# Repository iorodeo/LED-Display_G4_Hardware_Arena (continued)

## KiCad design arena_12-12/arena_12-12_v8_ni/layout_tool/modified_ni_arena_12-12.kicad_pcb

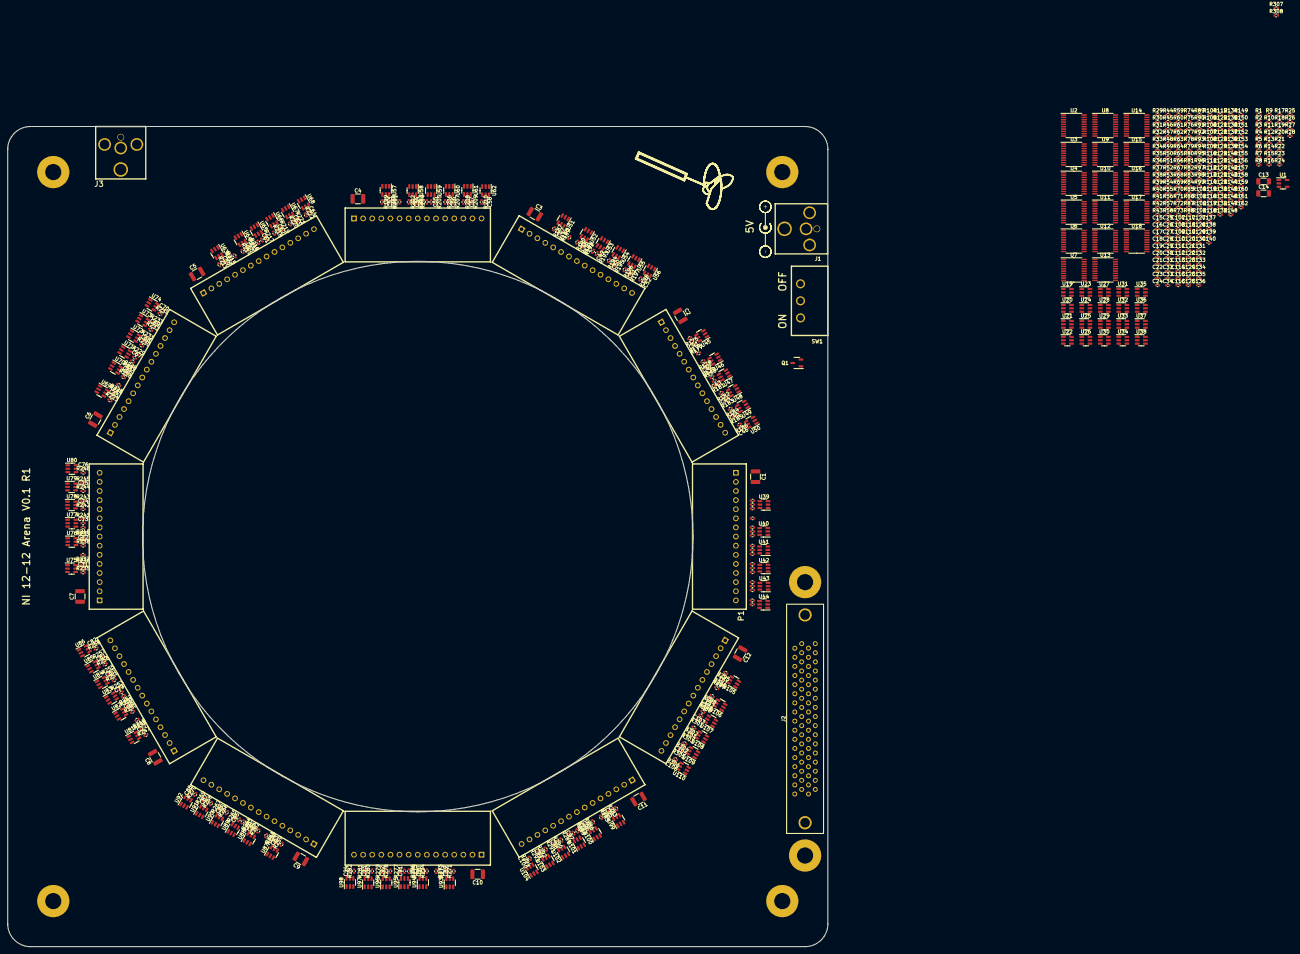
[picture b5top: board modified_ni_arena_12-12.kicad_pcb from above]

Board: 4 copper layers, 228.6 x 228.6 mm, 581 parts (0 on the bottom side), 658 nets, no tracks yet.

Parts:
C1, C2, C3, C4, C5, C6, C7, C8, C9, C10, C11, C12: 100uF; C_1210_3225Metric
C13, C14: 10uF; C_1206_3216Metric
C15, C16, C17, C18, C19, C20, C21, C22, C23, C24, C25, C26, C27, C28, C29, C30, C31, C32, C33, C34, C35, C36, C37, C38, C39, C40, C41, C42, C43, C44, C45, C46, C47, C48, C49, C50, C51, C52, C53, C54, C55, C56, C57, C58, C59, C60, C61, C62, C63, C64, C65, C66, C67, C68, C69, C70, C71, C72, C73, C74, C75, C76, C77, C78, C79, C80, C81, C82, C83, C84, C85, C86, C87, C88, C89, C90, C91, C92, C93, C94, C95, C96, C97, C98, C99, C100, C101, C102, C103, C104, C105, C106, C107, C108, C109, C110, C111, C112, C113, C114, C115, C116, C117, C118, C119, C120, C121, C122, C123, C124, C125, C126, C127, C128, C129, C130, C131, C132, C133, C134, C135, C136, C137, C138, C139, C140: 0.1uF; C_0402_1005Metric
H1, H2, H3, H4, H5, H6: MountingHole_Pad; MountingHole_4.5mm_Pad
J1, J3: Barrel_Jack; DCJACK_2PIN_HIGHCURRENT
J2: NI_TE_68pos; TE_CONN_DSUB_VERT_68
P1, P2, P3, P4, P5, P6, P7, P8, P9, P10, P11, P12: CONN15; HEADER_TOP
Q1: MOSFET_NCHAN; SOT-23-3
R1, R2, R3, R4, R5, R6, R7, R8, R9, R10, R11, R12, R13, R14, R15, R16, R17, R18, R19, R20, R21, R22, R23, R24, R25, R26, R27, R28, R29, R30, R31, R32, R33, R34, R35, R36, R37, R38, R39, R40, R41, R42, R43, R44, R45, R46, R47, R48, R49, R50, R51, R52, R53, R54, R55, R56, R57, R58, R59, R60, R61, R62, R63, R64, R65, R66, R67, R68, R69, R70, R71, R72, R73, R74, R75, R76, R77, R78, R79, R80, R81, R82, R83, R84, R85, R86, R87, R88, R89, R90, R91, R92, R93, R94, R95, R96, R97, R98, R99, R100, R101, R102, R103, R104, R105, R106, R107, R108, R109, R110, R111, R112, R113, R114, R115, R116, R117, R118, R119, R120, R121, R122, R123, R124, R125, R126, R127, R128, R129, R130, R131, R132, R133, R134, R135, R136, R137, R138, R139, R140, R141, R142, R143, R144, R145, R146, R147, R148, R149, R150, R151, R152, R153, R154, R155, R156, R157, R158, R159, R160, R161, R162, R163, R164, R165, R166, R167, R168, R169, R170, R171, R172, R173, R174, R175, R176, R177, R178, R179, R180, R181, R182, R183, R184, R185, R186, R187, R188, R189, R190, R191, R192, R193, R194, R195, R196, R197, R198, R199, R200, R201, R202, R203, R204, R205, R206, R207, R208, R209, R210, R211, R212, R213, R214, R215, R216, R217, R218, R219, R220, R221, R222, R223, R224, R225, R226, R227, R228, R229, R230, R231, R232, R233, R234, R235, R236, R237, R238, R239, R240, R241, R242, R243, R244, R245, R246, R247, R248, R249, R250, R251, R252, R253, R254, R255, R256, R257, R258, R259, R260, R261, R262, R263, R264, R265, R266, R267, R268, R269, R270, R271, R272, R273, R274, R275, R276, R277, R278, R279, R280, R281, R282, R283, R284, R285, R286, R287, R288, R289, R290, R291, R292, R293, R294, R295, R296, R297, R298, R299, R300, R301, R302, R303, R304, R305, R306: 33; R_0402_1005Metric
R307: 20k; R_0402_1005Metric
R308: 200; R_0402_1005Metric
SW1: SW_SPDT; slide_switch
U1: AP2112K-3.3; SOT-23-5
U2, U3, U4, U5, U6, U7, U8, U9, U10, U11, U12, U13, U14, U15, U16, U17, U18: TXB0108PW; TSSOP-20_4.4x6.5mm_P0.65mm
U19, U20, U21, U22, U23, U24, U25, U26, U27, U28, U29, U30, U31, U32, U33, U34, U35, U36, U37, U38, U39, U40, U41, U42, U43, U44, U45, U46, U47, U48, U49, U50, U51, U52, U53, U54, U55, U56, U57, U58, U59, U60, U61, U62, U63, U64, U65, U66, U67, U68, U69, U70, U71, U72, U73, U74, U75, U76, U77, U78, U79, U80, U81, U82, U83, U84, U85, U86, U87, U88, U89, U90, U91, U92, U93, U94, U95, U96, U97, U98, U99, U100, U101, U102, U103, U104, U105, U106, U107, U108, U109, U110: 74LVC2G17; SOT-23-6

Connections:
+3.3V: C14.1, C15.1, C16.1, C17.1, C18.1, C19.1, C20.1, C21.1, C22.1, C23.1, C24.1, C25.1, C26.1, C27.1, C28.1, C29.1, C30.1, C31.1, C32.1, C33.1, C34.1, C107.1, C109.1, C111.1, C113.1, C115.1, C117.1, C119.1, C121.1, C123.1, C125.1, C127.1, C129.1, C131.1, C133.1, C135.1, C137.1, C139.1, U1.5 (VOUT), U2.2 (VCCA), U2.10 (OE), U3.2 (VCCA), U3.10 (OE), U4.2 (VCCA), U4.10 (OE), U5.2 (VCCA), U5.10 (OE), U6.2 (VCCA), U6.10 (OE), U7.2 (VCCA), U7.10 (OE), U8.2 (VCCA), U8.10 (OE), U9.2 (VCCA), U9.10 (OE), U10.2 (VCCA), U10.10 (OE), U11.2 (VCCA), U11.10 (OE), U12.2 (VCCA), U12.10 (OE), U13.2 (VCCA), U13.10 (OE), U14.2 (VCCA), U14.10 (OE), U15.2 (VCCA), U15.10 (OE), U16.2 (VCCA), U16.10 (OE), U17.2 (VCCA), U17.10 (OE), U18.2 (VCCA), U18.10 (OE), U19.5 (VCC), U20.5 (VCC), U21.5 (VCC), U22.5 (VCC), U23.5 (VCC), U24.5 (VCC), U25.5 (VCC), U26.5 (VCC), U27.5 (VCC), U28.5 (VCC), U29.5 (VCC), U30.5 (VCC), U31.5 (VCC), U32.5 (VCC), U33.5 (VCC), U34.5 (VCC), U35.5 (VCC), U36.5 (VCC), U37.5 (VCC), U38.5 (VCC)
+5V: C1.1, C2.1, C3.1, C4.1, C5.1, C6.1, C7.1, C8.1, C9.1, C10.1, C11.1, C12.1, C13.1, C35.1, C36.1, C37.1, C38.1, C39.1, C40.1, C41.1, C42.1, C43.1, C44.1, C45.1, C46.1, C47.1, C48.1, C49.1, C50.1, C51.1, C52.1, C53.1, C54.1, C55.1, C56.1, C57.1, C58.1, C59.1, C60.1, C61.1, C62.1, C63.1, C64.1, C65.1, C66.1, C67.1, C68.1, C69.1, C70.1, C71.1, C72.1, C73.1, C74.1, C75.1, C76.1, C77.1, C78.1, C79.1, C80.1, C81.1, C82.1, C83.1, C84.1, C85.1, C86.1, C87.1, C88.1, C89.1, C90.1, C91.1, C92.1, C93.1, C94.1, C95.1, C96.1, C97.1, C98.1, C99.1, C100.1, C101.1, C102.1, C103.1, C104.1, C105.1, C106.1, C108.1, C110.1, C112.1, C114.1, C116.1, C118.1, C120.1, C122.1, C124.1, C126.1, C128.1, C130.1, C132.1, C134.1, C136.1, C138.1, C140.1, J3.1, P1.1, P2.1, P3.1, P4.1, P5.1, P6.1, P7.1, P8.1, P9.1, P10.1, P11.1, P12.1, SW1.2 (B), U1.1 (VIN), U1.3 (EN), U2.19 (VCCB), U3.19 (VCCB), U4.19 (VCCB), U5.19 (VCCB), U6.19 (VCCB), U7.19 (VCCB), U8.19 (VCCB), U9.19 (VCCB), U10.19 (VCCB), U11.19 (VCCB), U12.19 (VCCB), U13.19 (VCCB), U14.19 (VCCB), U15.19 (VCCB), U16.19 (VCCB), U17.19 (VCCB), U18.19 (VCCB), U39.5 (VCC), U40.5 (VCC), U41.5 (VCC), U42.5 (VCC), U43.5 (VCC), U44.5 (VCC), U45.5 (VCC), U46.5 (VCC), U47.5 (VCC), U48.5 (VCC), U49.5 (VCC), U50.5 (VCC), U51.5 (VCC), U52.5 (VCC), U53.5 (VCC), U54.5 (VCC), U55.5 (VCC), U56.5 (VCC), U57.5 (VCC), U58.5 (VCC), U59.5 (VCC), U60.5 (VCC), U61.5 (VCC), U62.5 (VCC), U63.5 (VCC), U64.5 (VCC), U65.5 (VCC), U66.5 (VCC), U67.5 (VCC), U68.5 (VCC), U69.5 (VCC), U70.5 (VCC), U71.5 (VCC), U72.5 (VCC), U73.5 (VCC), U74.5 (VCC), U75.5 (VCC), U76.5 (VCC), U77.5 (VCC), U78.5 (VCC), U79.5 (VCC), U80.5 (VCC), U81.5 (VCC), U82.5 (VCC), U83.5 (VCC), U84.5 (VCC), U85.5 (VCC), U86.5 (VCC), U87.5 (VCC), U88.5 (VCC), U89.5 (VCC), U90.5 (VCC), U91.5 (VCC), U92.5 (VCC), U93.5 (VCC), U94.5 (VCC), U95.5 (VCC), U96.5 (VCC), U97.5 (VCC), U98.5 (VCC), U99.5 (VCC), U100.5 (VCC), U101.5 (VCC), U102.5 (VCC), U103.5 (VCC), U104.5 (VCC), U105.5 (VCC), U106.5 (VCC), U107.5 (VCC), U108.5 (VCC), U109.5 (VCC), U110.5 (VCC)
/Level Shifters/PAN3V.CS_0: R1.2, U19.1
/Level Shifters/PAN3V.CS_1: R2.2, U19.3
/Level Shifters/PAN3V.CS_2: R3.2, U20.1
/Level Shifters/PAN3V.CS_3: R4.2, U20.3
/Level Shifters/PAN3V.CS_4: R5.2, U21.1
/Level Shifters/PAN3V.CS_5: R6.2, U21.3
/Level Shifters/PAN3V.CS_6: R7.2, U22.1
/Level Shifters/PAN3V.CS_7: R8.2, U22.3
/Level Shifters/PAN3V.EXT_INT: R22.2, U38.1
/Level Shifters/PAN3V.MISO_00: J2.50, R149.2
/Level Shifters/PAN3V.MISO_01: J2.52, R150.2
/Level Shifters/PAN3V.MISO_02: J2.54, R151.2
/Level Shifters/PAN3V.MISO_03: J2.56, R152.2
/Level Shifters/PAN3V.MISO_04: J2.58, R153.2
/Level Shifters/PAN3V.MISO_05: J2.60, R154.2
/Level Shifters/PAN3V.MISO_06: J2.62, R155.2
/Level Shifters/PAN3V.MISO_07: J2.63, R156.2
/Level Shifters/PAN3V.MISO_08: J2.64, R159.1
/Level Shifters/PAN3V.MISO_09: J2.65, R160.1
/Level Shifters/PAN3V.MISO_10: J2.66, R161.1
/Level Shifters/PAN3V.MISO_11: J2.67, R162.1
/Level Shifters/PAN3V.MOSI_00: R15.2, U26.1
/Level Shifters/PAN3V.MOSI_01: R16.2, U26.3
/Level Shifters/PAN3V.MOSI_02: R17.2, U27.1
/Level Shifters/PAN3V.MOSI_03: R18.2, U27.3
/Level Shifters/PAN3V.MOSI_04: R19.2, U32.1
/Level Shifters/PAN3V.MOSI_05: R20.2, U32.3
/Level Shifters/PAN3V.MOSI_06: R21.2, U34.1
/Level Shifters/PAN3V.MOSI_07: R23.2, U34.3
/Level Shifters/PAN3V.MOSI_08: R24.2, U33.1
/Level Shifters/PAN3V.MOSI_09: R25.2, U33.3
/Level Shifters/PAN3V.MOSI_10: R26.2, U35.1
/Level Shifters/PAN3V.MOSI_11: R27.2, U35.3
/Level Shifters/PAN3V.RESET: R28.2, U38.3
/Level Shifters/PAN3V.SCK_0: R9.2, U23.1
/Level Shifters/PAN3V.SCK_1: R10.2, U23.3
/Level Shifters/PAN3V.SCK_2: R11.2, U24.1
/Level Shifters/PAN3V.SCK_3: R12.2, U24.3
/Level Shifters/PAN3V.SCK_4: R13.2, U25.1
/Level Shifters/PAN3V.SCK_5: R14.2, U25.3
/Level Shifters/PAN5V.CS_0_P01: R29.1, U40.3
/Level Shifters/PAN5V.CS_0_P02: R30.1, U46.1
/Level Shifters/PAN5V.CS_0_P03: R31.1, U52.1
/Level Shifters/PAN5V.CS_0_P04: R32.1, U58.1
/Level Shifters/PAN5V.CS_0_P05: R33.1, U64.1
/Level Shifters/PAN5V.CS_0_P06: R34.1, U70.1
/Level Shifters/PAN5V.CS_0_P07: R35.1, U76.1
/Level Shifters/PAN5V.CS_0_P08: R36.1, U82.1
/Level Shifters/PAN5V.CS_0_P09: R37.1, U88.1
/Level Shifters/PAN5V.CS_0_P10: R38.1, U94.1
/Level Shifters/PAN5V.CS_0_P11: R39.1, U100.1
/Level Shifters/PAN5V.CS_0_P12: R40.1, U106.1
/Level Shifters/PAN5V.CS_1_P01: R41.1, U40.1
/Level Shifters/PAN5V.CS_1_P02: R42.1, U46.3
/Level Shifters/PAN5V.CS_1_P03: R43.1, U52.3
/Level Shifters/PAN5V.CS_1_P04: R44.1, U58.3
/Level Shifters/PAN5V.CS_1_P05: R45.1, U64.3
/Level Shifters/PAN5V.CS_1_P06: R46.1, U70.3
/Level Shifters/PAN5V.CS_1_P07: R47.1, U76.3
/Level Shifters/PAN5V.CS_1_P08: R48.1, U82.3
/Level Shifters/PAN5V.CS_1_P09: R49.1, U88.3
/Level Shifters/PAN5V.CS_1_P10: R50.1, U94.3
/Level Shifters/PAN5V.CS_1_P11: R51.1, U100.3
/Level Shifters/PAN5V.CS_1_P12: R52.1, U106.3
/Level Shifters/PAN5V.CS_2_P01: R53.1, U41.3
/Level Shifters/PAN5V.CS_2_P02: R54.1, U47.1
/Level Shifters/PAN5V.CS_2_P03: R55.1, U53.1
/Level Shifters/PAN5V.CS_2_P04: R56.1, U59.1
/Level Shifters/PAN5V.CS_2_P05: R57.1, U65.1
/Level Shifters/PAN5V.CS_2_P06: R58.1, U71.1
/Level Shifters/PAN5V.CS_2_P07: R59.1, U77.1
/Level Shifters/PAN5V.CS_2_P08: R60.1, U83.1
/Level Shifters/PAN5V.CS_2_P09: R61.1, U89.1
/Level Shifters/PAN5V.CS_2_P10: R62.1, U95.1
/Level Shifters/PAN5V.CS_2_P11: R63.1, U101.1
/Level Shifters/PAN5V.CS_2_P12: R64.1, U107.1
/Level Shifters/PAN5V.CS_3_P01: R65.1, U41.1
/Level Shifters/PAN5V.CS_3_P02: R66.1, U47.3
/Level Shifters/PAN5V.CS_3_P03: R67.1, U53.3
/Level Shifters/PAN5V.CS_3_P04: R68.1, U59.3
/Level Shifters/PAN5V.CS_3_P05: R69.1, U65.3
/Level Shifters/PAN5V.CS_3_P06: R70.1, U71.3
/Level Shifters/PAN5V.CS_3_P07: R71.1, U77.3
/Level Shifters/PAN5V.CS_3_P08: R72.1, U83.3
/Level Shifters/PAN5V.CS_3_P09: R73.1, U89.3
/Level Shifters/PAN5V.CS_3_P10: R74.1, U95.3
/Level Shifters/PAN5V.CS_3_P11: R75.1, U101.3
/Level Shifters/PAN5V.CS_3_P12: R76.1, U107.3
/Level Shifters/PAN5V.CS_4_P01: R77.1, U42.3
/Level Shifters/PAN5V.CS_4_P02: R78.1, U48.1
/Level Shifters/PAN5V.CS_4_P03: R79.1, U54.1
/Level Shifters/PAN5V.CS_4_P04: R80.1, U60.1
/Level Shifters/PAN5V.CS_4_P05: R81.1, U66.1
/Level Shifters/PAN5V.CS_4_P06: R82.1, U72.1
/Level Shifters/PAN5V.CS_4_P07: R83.1, U78.1
/Level Shifters/PAN5V.CS_4_P08: R84.1, U84.1
/Level Shifters/PAN5V.CS_4_P09: R85.1, U90.1
/Level Shifters/PAN5V.CS_4_P10: R86.1, U96.1
/Level Shifters/PAN5V.CS_4_P11: R87.1, U102.1
/Level Shifters/PAN5V.CS_4_P12: R88.1, U108.1
/Level Shifters/PAN5V.CS_5_P01: R89.1, U42.1
/Level Shifters/PAN5V.CS_5_P02: R90.1, U48.3
/Level Shifters/PAN5V.CS_5_P03: R91.1, U54.3
/Level Shifters/PAN5V.CS_5_P04: R92.1, U60.3
/Level Shifters/PAN5V.CS_5_P05: R93.1, U66.3
/Level Shifters/PAN5V.CS_5_P06: R94.1, U72.3
/Level Shifters/PAN5V.CS_5_P07: R95.1, U78.3
/Level Shifters/PAN5V.CS_5_P08: R96.1, U84.3
/Level Shifters/PAN5V.CS_5_P09: R97.1, U90.3
/Level Shifters/PAN5V.CS_5_P10: R98.1, U96.3
/Level Shifters/PAN5V.CS_5_P11: R99.1, U102.3
/Level Shifters/PAN5V.CS_5_P12: R100.1, U108.3
/Level Shifters/PAN5V.CS_6_P01: R101.1, U43.3
/Level Shifters/PAN5V.CS_6_P02: R102.1, U49.1
/Level Shifters/PAN5V.CS_6_P03: R103.1, U55.1
/Level Shifters/PAN5V.CS_6_P04: R104.1, U61.1
/Level Shifters/PAN5V.CS_6_P05: R105.1, U67.1
/Level Shifters/PAN5V.CS_6_P06: R106.1, U73.1
/Level Shifters/PAN5V.CS_6_P07: R107.1, U79.1
/Level Shifters/PAN5V.CS_6_P08: R108.1, U85.1
/Level Shifters/PAN5V.CS_6_P09: R109.1, U91.1
/Level Shifters/PAN5V.CS_6_P10: R110.1, U97.1
/Level Shifters/PAN5V.CS_6_P11: R111.1, U103.1
/Level Shifters/PAN5V.CS_6_P12: R112.1, U109.1
/Level Shifters/PAN5V.CS_7_P01: R113.1, U43.1
/Level Shifters/PAN5V.CS_7_P02: R114.1, U49.3
/Level Shifters/PAN5V.CS_7_P03: R115.1, U55.3
/Level Shifters/PAN5V.CS_7_P04: R116.1, U61.3
/Level Shifters/PAN5V.CS_7_P05: R117.1, U67.3
/Level Shifters/PAN5V.CS_7_P06: R118.1, U73.3
/Level Shifters/PAN5V.CS_7_P07: R119.1, U79.3
/Level Shifters/PAN5V.CS_7_P08: R120.1, U85.3
/Level Shifters/PAN5V.CS_7_P09: R121.1, U91.3
/Level Shifters/PAN5V.CS_7_P10: R122.1, U97.3
/Level Shifters/PAN5V.CS_7_P11: R123.1, U103.3
/Level Shifters/PAN5V.CS_7_P12: R124.1, U109.3
/Level Shifters/PAN5V.EXT_INT: R157.1, U44.3, U50.1, U56.1, U62.1, U68.1, U74.1, U80.1, U86.1, U92.1, U98.1, U104.1, U110.1
/Level Shifters/PAN5V.MISO_00: R165.1, U28.1
/Level Shifters/PAN5V.MISO_01: R177.1, U28.3
/Level Shifters/PAN5V.MISO_02: R189.1, U29.1
/Level Shifters/PAN5V.MISO_03: R201.1, U29.3
/Level Shifters/PAN5V.MISO_04: R213.1, U30.1
/Level Shifters/PAN5V.MISO_05: R225.1, U30.3
/Level Shifters/PAN5V.MISO_06: R237.1, U31.1
/Level Shifters/PAN5V.MISO_07: R249.1, U31.3
/Level Shifters/PAN5V.MISO_08: R261.1, U36.1
/Level Shifters/PAN5V.MISO_09: R273.1, U36.3
/Level Shifters/PAN5V.MISO_10: R285.1, U37.1
/Level Shifters/PAN5V.MISO_11: R297.1, U37.3
/Level Shifters/PAN5V.MOSI_00: R137.1, U39.1
/Level Shifters/PAN5V.MOSI_01: R138.1, U45.3
/Level Shifters/PAN5V.MOSI_02: R139.1, U51.3
/Level Shifters/PAN5V.MOSI_03: R140.1, U57.3
/Level Shifters/PAN5V.MOSI_04: R141.1, U63.3
/Level Shifters/PAN5V.MOSI_05: R142.1, U69.3
/Level Shifters/PAN5V.MOSI_06: R143.1, U75.3
/Level Shifters/PAN5V.MOSI_07: R144.1, U81.3
/Level Shifters/PAN5V.MOSI_08: R145.1, U87.3
/Level Shifters/PAN5V.MOSI_09: R146.1, U93.3
/Level Shifters/PAN5V.MOSI_10: R147.1, U99.3
/Level Shifters/PAN5V.MOSI_11: R148.1, U105.3
/Level Shifters/PAN5V.RESET: R158.1, R308.2
/Level Shifters/PAN5V.SCK_0_H1: R125.1, U39.3
/Level Shifters/PAN5V.SCK_0_H2: R126.1, U75.1
/Level Shifters/PAN5V.SCK_1_H1: R127.1, U45.1
/Level Shifters/PAN5V.SCK_1_H2: R128.1, U81.1
/Level Shifters/PAN5V.SCK_2_H1: R129.1, U51.1
/Level Shifters/PAN5V.SCK_2_H2: R130.1, U87.1
/Level Shifters/PAN5V.SCK_3_H1: R131.1, U57.1
/Level Shifters/PAN5V.SCK_3_H2: R132.1, U93.1
/Level Shifters/PAN5V.SCK_4_H1: R133.1, U63.1
/Level Shifters/PAN5V.SCK_4_H2: R134.1, U99.1
/Level Shifters/PAN5V.SCK_5_H1: R135.1, U69.1
/Level Shifters/PAN5V.SCK_5_H2: R136.1, U105.1
/Panel Headers/CS_00_P01: P1.7, R166.2
/Panel Headers/CS_00_P02: P2.7, R178.2
/Panel Headers/CS_00_P03: P3.7, R190.2
/Panel Headers/CS_00_P04: P4.7, R202.2
/Panel Headers/CS_00_P05: P5.7, R214.2
/Panel Headers/CS_00_P06: P6.7, R226.2
/Panel Headers/CS_00_P07: P7.7, R238.2
/Panel Headers/CS_00_P08: P8.7, R250.2
/Panel Headers/CS_00_P09: P9.7, R262.2
/Panel Headers/CS_00_P10: P10.7, R274.2
/Panel Headers/CS_00_P11: P11.7, R286.2
/Panel Headers/CS_00_P12: P12.7, R298.2
/Panel Headers/CS_01_P01: P1.8, R167.2
/Panel Headers/CS_01_P02: P2.8, R179.2
/Panel Headers/CS_01_P03: P3.8, R191.2
/Panel Headers/CS_01_P04: P4.8, R203.2
/Panel Headers/CS_01_P05: P5.8, R215.2
/Panel Headers/CS_01_P06: P6.8, R227.2
/Panel Headers/CS_01_P07: P7.8, R239.2
/Panel Headers/CS_01_P08: P8.8, R251.2
/Panel Headers/CS_01_P09: P9.8, R263.2
/Panel Headers/CS_01_P10: P10.8, R275.2
/Panel Headers/CS_01_P11: P11.8, R287.2
/Panel Headers/CS_01_P12: P12.8, R299.2
/Panel Headers/CS_02_P01: P1.9, R168.2
/Panel Headers/CS_02_P02: P2.9, R180.2
/Panel Headers/CS_02_P03: P3.9, R192.2
/Panel Headers/CS_02_P04: P4.9, R204.2
/Panel Headers/CS_02_P05: P5.9, R216.2
/Panel Headers/CS_02_P06: P6.9, R228.2
/Panel Headers/CS_02_P07: P7.9, R240.2
/Panel Headers/CS_02_P08: P8.9, R252.2
/Panel Headers/CS_02_P09: P9.9, R264.2
/Panel Headers/CS_02_P10: P10.9, R276.2
/Panel Headers/CS_02_P11: P11.9, R288.2
/Panel Headers/CS_02_P12: P12.9, R300.2
/Panel Headers/CS_03_P01: P1.10, R169.2
/Panel Headers/CS_03_P02: P2.10, R181.2
/Panel Headers/CS_03_P03: P3.10, R193.2
/Panel Headers/CS_03_P04: P4.10, R205.2
/Panel Headers/CS_03_P05: P5.10, R217.2
/Panel Headers/CS_03_P06: P6.10, R229.2
/Panel Headers/CS_03_P07: P7.10, R241.2
/Panel Headers/CS_03_P08: P8.10, R253.2
/Panel Headers/CS_03_P09: P9.10, R265.2
/Panel Headers/CS_03_P10: P10.10, R277.2
/Panel Headers/CS_03_P11: P11.10, R289.2
/Panel Headers/CS_03_P12: P12.10, R301.2
/Panel Headers/CS_04_P01: P1.11, R170.2
/Panel Headers/CS_04_P02: P2.11, R182.2
/Panel Headers/CS_04_P03: P3.11, R194.2
/Panel Headers/CS_04_P04: P4.11, R206.2
/Panel Headers/CS_04_P05: P5.11, R218.2
/Panel Headers/CS_04_P06: P6.11, R230.2
/Panel Headers/CS_04_P07: P7.11, R242.2
/Panel Headers/CS_04_P08: P8.11, R254.2
/Panel Headers/CS_04_P09: P9.11, R266.2
/Panel Headers/CS_04_P10: P10.11, R278.2
/Panel Headers/CS_04_P11: P11.11, R290.2
/Panel Headers/CS_04_P12: P12.11, R302.2
/Panel Headers/CS_05_P01: P1.12, R171.2
/Panel Headers/CS_05_P02: P2.12, R183.2
/Panel Headers/CS_05_P03: P3.12, R195.2
/Panel Headers/CS_05_P04: P4.12, R207.2
/Panel Headers/CS_05_P05: P5.12, R219.2
/Panel Headers/CS_05_P06: P6.12, R231.2
/Panel Headers/CS_05_P07: P7.12, R243.2
/Panel Headers/CS_05_P08: P8.12, R255.2
/Panel Headers/CS_05_P09: P9.12, R267.2
/Panel Headers/CS_05_P10: P10.12, R279.2
/Panel Headers/CS_05_P11: P11.12, R291.2
/Panel Headers/CS_05_P12: P12.12, R303.2
/Panel Headers/CS_06_P01: P1.13, R172.2
/Panel Headers/CS_06_P02: P2.13, R184.2
/Panel Headers/CS_06_P03: P3.13, R196.2
/Panel Headers/CS_06_P04: P4.13, R208.2
/Panel Headers/CS_06_P05: P5.13, R220.2
/Panel Headers/CS_06_P06: P6.13, R232.2
/Panel Headers/CS_06_P07: P7.13, R244.2
/Panel Headers/CS_06_P08: P8.13, R256.2
/Panel Headers/CS_06_P09: P9.13, R268.2
/Panel Headers/CS_06_P10: P10.13, R280.2
/Panel Headers/CS_06_P11: P11.13, R292.2
/Panel Headers/CS_06_P12: P12.13, R304.2
/Panel Headers/CS_07_P01: P1.14, R173.2
/Panel Headers/CS_07_P02: P2.14, R185.2
/Panel Headers/CS_07_P03: P3.14, R197.2
/Panel Headers/CS_07_P04: P4.14, R209.2
/Panel Headers/CS_07_P05: P5.14, R221.2
/Panel Headers/CS_07_P06: P6.14, R233.2
/Panel Headers/CS_07_P07: P7.14, R245.2
/Panel Headers/CS_07_P08: P8.14, R257.2
/Panel Headers/CS_07_P09: P9.14, R269.2
/Panel Headers/CS_07_P10: P10.14, R281.2
/Panel Headers/CS_07_P11: P11.14, R293.2
/Panel Headers/CS_07_P12: P12.14, R305.2
/Panel Headers/EXT_INT_P01: P1.15, R174.2
/Panel Headers/EXT_INT_P02: P2.15, R186.2
/Panel Headers/EXT_INT_P03: P3.15, R198.2
/Panel Headers/EXT_INT_P04: P4.15, R210.2
/Panel Headers/EXT_INT_P05: P5.15, R222.2
/Panel Headers/EXT_INT_P06: P6.15, R234.2
/Panel Headers/EXT_INT_P07: P7.15, R246.2
/Panel Headers/EXT_INT_P08: P8.15, R258.2
/Panel Headers/EXT_INT_P09: P9.15, R270.2
/Panel Headers/EXT_INT_P10: P10.15, R282.2
/Panel Headers/EXT_INT_P11: P11.15, R294.2
/Panel Headers/EXT_INT_P12: P12.15, R306.2
/Panel Headers/MISO_00_P01: P1.6, R165.2
/Panel Headers/MISO_01_P02: P2.6, R177.2
/Panel Headers/MISO_02_P03: P3.6, R189.2
/Panel Headers/MISO_03_P04: P4.6, R201.2
/Panel Headers/MISO_04_P05: P5.6, R213.2
/Panel Headers/MISO_05_P06: P6.6, R225.2
/Panel Headers/MISO_06_P07: P7.6, R237.2
/Panel Headers/MISO_07_P08: P8.6, R249.2
/Panel Headers/MISO_08_P09: P9.6, R261.2
/Panel Headers/MISO_09_P10: P10.6, R273.2
/Panel Headers/MISO_10_P11: P11.6, R285.2
/Panel Headers/MISO_11_P12: P12.6, R297.2
/Panel Headers/MOSI_00_P01: P1.5, R164.2
/Panel Headers/MOSI_01_P02: P2.5, R176.2
/Panel Headers/MOSI_02_P03: P3.5, R188.2
/Panel Headers/MOSI_03_P04: P4.5, R200.2
/Panel Headers/MOSI_04_P05: P5.5, R212.2
/Panel Headers/MOSI_05_P06: P6.5, R224.2
/Panel Headers/MOSI_06_P07: P7.5, R236.2
/Panel Headers/MOSI_07_P08: P8.5, R248.2
/Panel Headers/MOSI_08_P09: P9.5, R260.2
/Panel Headers/MOSI_09_P10: P10.5, R272.2
/Panel Headers/MOSI_10_P11: P11.5, R284.2
/Panel Headers/MOSI_11_P12: P12.5, R296.2
/Panel Headers/RESET: P1.3, P2.3, P3.3, P4.3, P5.3, P6.3, P7.3, P8.3, P9.3, P10.3, P11.3, P12.3, Q1.3 (D)
/Panel Headers/SCK_0_H1_P01: P1.4, R163.2
/Panel Headers/SCK_0_H2_P07: P7.4, R235.2
/Panel Headers/SCK_1_H1_P02: P2.4, R175.2
/Panel Headers/SCK_1_H2_P08: P8.4, R247.2
/Panel Headers/SCK_2_H1_P03: P3.4, R187.2
/Panel Headers/SCK_2_H2_P09: P9.4, R259.2
/Panel Headers/SCK_3_H1_P04: P4.4, R199.2
/Panel Headers/SCK_3_H2_P10: P10.4, R271.2
/Panel Headers/SCK_4_H1_P05: P5.4, R211.2
/Panel Headers/SCK_4_H2_P11: P11.4, R283.2
/Panel Headers/SCK_5_H1_P06: P6.4, R223.2
/Panel Headers/SCK_5_H2_P12: P12.4, R295.2
/Power & Voltage Regulators/SW_5V: J1.1, SW1.1 (A)
GND: C1.2, C2.2, C3.2, C4.2, C5.2, C6.2, C7.2, C8.2, C9.2, C10.2, C11.2, C12.2, C13.2, C14.2, C15.2, C16.2, C17.2, C18.2, C19.2, C20.2, C21.2, C22.2, C23.2, C24.2, C25.2, C26.2, C27.2, C28.2, C29.2, C30.2, C31.2, C32.2, C33.2, C34.2, C35.2, C36.2, C37.2, C38.2, C39.2, C40.2, C41.2, C42.2, C43.2, C44.2, C45.2, C46.2, C47.2, C48.2, C49.2, C50.2, C51.2, C52.2, C53.2, C54.2, C55.2, C56.2, C57.2, C58.2, C59.2, C60.2, C61.2, C62.2, C63.2, C64.2, C65.2, C66.2, C67.2, C68.2, C69.2, C70.2, C71.2, C72.2, C73.2, C74.2, C75.2, C76.2, C77.2, C78.2, C79.2, C80.2, C81.2, C82.2, C83.2, C84.2, C85.2, C86.2, C87.2, C88.2, C89.2, C90.2, C91.2, C92.2, C93.2, C94.2, C95.2, C96.2, C97.2, C98.2, C99.2, C100.2, C101.2, C102.2, C103.2, C104.2, C105.2, C106.2, C107.2, C108.2, C109.2, C110.2, C111.2, C112.2, C113.2, C114.2, C115.2, C116.2, C117.2, C118.2, C119.2, C120.2, C121.2, C122.2, C123.2, C124.2, C125.2, C126.2, C127.2, C128.2, C129.2, C130.2, C131.2, C132.2, C133.2, C134.2, C135.2, C136.2, C137.2, C138.2, C139.2, C140.2, H1.1, H2.1, H3.1, H4.1, H5.1, H6.1, J1.2, J2.1, J2.2, J2.3, J2.69 (GND), J2.70 (GND), J3.2, P1.2, P2.2, P3.2, P4.2, P5.2, P6.2, P7.2, P8.2, P9.2, P10.2, P11.2, P12.2, Q1.2 (S), R307.1, SW1.3 (C), U1.2 (GND), U2.11 (GND), U3.11 (GND), U4.11 (GND), U5.11 (GND), U6.11 (GND), U7.11 (GND), U8.11 (GND), U9.11 (GND), U10.11 (GND), U11.11 (GND), U12.11 (GND), U13.11 (GND), U14.11 (GND), U15.11 (GND), U16.11 (GND), U17.11 (GND), U18.11 (GND), U19.2 (GND), U20.2 (GND), U21.2 (GND), U22.2 (GND), U23.2 (GND), U24.2 (GND), U25.2 (GND), U26.2 (GND), U27.2 (GND), U28.2 (GND), U29.2 (GND), U30.2 (GND), U31.2 (GND), U32.2 (GND), U33.2 (GND), U34.2 (GND), U35.2 (GND), U36.2 (GND), U37.2 (GND), U38.2 (GND), U39.2 (GND), U40.2 (GND), U41.2 (GND), U42.2 (GND), U43.2 (GND), U44.2 (GND), U45.2 (GND), U46.2 (GND), U47.2 (GND), U48.2 (GND), U49.2 (GND), U50.2 (GND), U51.2 (GND), U52.2 (GND), U53.2 (GND), U54.2 (GND), U55.2 (GND), U56.2 (GND), U57.2 (GND), U58.2 (GND), U59.2 (GND), U60.2 (GND), U61.2 (GND), U62.2 (GND), U63.2 (GND), U64.2 (GND), U65.2 (GND), U66.2 (GND), U67.2 (GND), U68.2 (GND), U69.2 (GND), U70.2 (GND), U71.2 (GND), U72.2 (GND), U73.2 (GND), U74.2 (GND), U75.2 (GND), U76.2 (GND), U77.2 (GND), U78.2 (GND), U79.2 (GND), U80.2 (GND), U81.2 (GND), U82.2 (GND), U83.2 (GND), U84.2 (GND), U85.2 (GND), U86.2 (GND), U87.2 (GND), U88.2 (GND), U89.2 (GND), U90.2 (GND), U91.2 (GND), U92.2 (GND), U93.2 (GND), U94.2 (GND), U95.2 (GND), U96.2 (GND), U97.2 (GND), U98.2 (GND), U99.2 (GND), U100.2 (GND), U101.2 (GND), U102.2 (GND), U103.2 (GND), U104.2 (GND), U105.2 (GND), U106.2 (GND), U107.2 (GND), U108.2 (GND), U109.2 (GND), U110.2 (GND)
unnamed: J2.29, R23.1
unnamed: J2.30, R24.1
unnamed: J2.31, R25.1
unnamed: J2.32, R26.1
unnamed: J2.33, R27.1
unnamed: J2.34, R28.1
unnamed: J2.35, R1.1
unnamed: J2.36, R2.1
unnamed: J2.37, R3.1
unnamed: J2.38, R4.1
unnamed: J2.39, R5.1
unnamed: J2.40, R6.1
unnamed: J2.41, R7.1
unnamed: J2.42, R8.1
unnamed: J2.43, R9.1
unnamed: J2.44, R10.1
unnamed: J2.45, R11.1
unnamed: J2.46, R12.1
unnamed: J2.47, R13.1
unnamed: J2.48, R14.1
unnamed: J2.49, R15.1
unnamed: J2.51, R16.1
unnamed: J2.53, R17.1
unnamed: J2.55, R18.1
unnamed: J2.57, R19.1
unnamed: J2.59, R20.1
unnamed: J2.61, R21.1
unnamed: J2.68, R22.1
unnamed: Q1.1 (G), R307.2, R308.1
unnamed: R163.1, U39.4
unnamed: R164.1, U39.6
unnamed: R166.1, U40.4
unnamed: R167.1, U40.6
unnamed: R168.1, U41.4
unnamed: R169.1, U41.6
unnamed: R170.1, U42.4
unnamed: R171.1, U42.6
unnamed: R172.1, U43.4
unnamed: R173.1, U43.6
unnamed: R174.1, U44.4
unnamed: R175.1, U45.6
unnamed: R176.1, U45.4
unnamed: R178.1, U46.6
unnamed: R179.1, U46.4
unnamed: R180.1, U47.6
unnamed: R181.1, U47.4
unnamed: R182.1, U48.6
unnamed: R183.1, U48.4
unnamed: R184.1, U49.6
unnamed: R185.1, U49.4
unnamed: R186.1, U50.6
unnamed: R187.1, U51.6
unnamed: R188.1, U51.4
unnamed: R190.1, U52.6
unnamed: R191.1, U52.4
unnamed: R192.1, U53.6
unnamed: R193.1, U53.4
unnamed: R194.1, U54.6
unnamed: R195.1, U54.4
unnamed: R196.1, U55.6
unnamed: R197.1, U55.4
unnamed: R198.1, U56.6
unnamed: R199.1, U57.6
unnamed: R200.1, U57.4
unnamed: R202.1, U58.6
unnamed: R203.1, U58.4
unnamed: R204.1, U59.6
unnamed: R205.1, U59.4
unnamed: R206.1, U60.6
unnamed: R207.1, U60.4
unnamed: R208.1, U61.6
unnamed: R209.1, U61.4
unnamed: R210.1, U62.6
unnamed: R211.1, U63.6
unnamed: R212.1, U63.4
unnamed: R214.1, U64.6
unnamed: R215.1, U64.4
unnamed: R216.1, U65.6
unnamed: R217.1, U65.4
unnamed: R218.1, U66.6
unnamed: R219.1, U66.4
unnamed: R220.1, U67.6
unnamed: R221.1, U67.4
unnamed: R222.1, U68.6
unnamed: R223.1, U69.6
unnamed: R224.1, U69.4
unnamed: R226.1, U70.6
unnamed: R227.1, U70.4
unnamed: R228.1, U71.6
unnamed: R229.1, U71.4
unnamed: R230.1, U72.6
unnamed: R231.1, U72.4
unnamed: R232.1, U73.6
unnamed: R233.1, U73.4
unnamed: R234.1, U74.6
unnamed: R235.1, U75.6
unnamed: R236.1, U75.4
unnamed: R238.1, U76.6
unnamed: R239.1, U76.4
unnamed: R240.1, U77.6
unnamed: R241.1, U77.4
unnamed: R242.1, U78.6
unnamed: R243.1, U78.4
unnamed: R244.1, U79.6
unnamed: R245.1, U79.4
unnamed: R246.1, U80.6
unnamed: R247.1, U81.6
unnamed: R248.1, U81.4
unnamed: R250.1, U82.6
unnamed: R251.1, U82.4
unnamed: R252.1, U83.6
unnamed: R253.1, U83.4
unnamed: R254.1, U84.6
unnamed: R255.1, U84.4
unnamed: R256.1, U85.6
unnamed: R257.1, U85.4
unnamed: R258.1, U86.6
unnamed: R259.1, U87.6
unnamed: R260.1, U87.4
unnamed: R262.1, U88.6
unnamed: R263.1, U88.4
unnamed: R264.1, U89.6
unnamed: R265.1, U89.4
unnamed: R266.1, U90.6
unnamed: R267.1, U90.4
unnamed: R268.1, U91.6
unnamed: R269.1, U91.4
unnamed: R270.1, U92.6
unnamed: R271.1, U93.6
unnamed: R272.1, U93.4
unnamed: R274.1, U94.6
unnamed: R275.1, U94.4
unnamed: R276.1, U95.6
unnamed: R277.1, U95.4
unnamed: R278.1, U96.6
unnamed: R279.1, U96.4
unnamed: R280.1, U97.6
unnamed: R281.1, U97.4
unnamed: R282.1, U98.6
unnamed: R283.1, U99.6
unnamed: R284.1, U99.4
unnamed: R286.1, U100.6
unnamed: R287.1, U100.4
unnamed: R288.1, U101.6
unnamed: R289.1, U101.4
unnamed: R290.1, U102.6
unnamed: R291.1, U102.4
unnamed: R292.1, U103.6
unnamed: R293.1, U103.4
unnamed: R294.1, U104.6
unnamed: R295.1, U105.6
unnamed: R296.1, U105.4
unnamed: R298.1, U106.6
unnamed: R299.1, U106.4
unnamed: R300.1, U107.6
unnamed: R301.1, U107.4
unnamed: R302.1, U108.6
unnamed: R303.1, U108.4
unnamed: R304.1, U109.6
unnamed: R305.1, U109.4
unnamed: R306.1, U110.6
unnamed: U2.1 (A1), U2.3 (A2), U2.4 (A3), U2.5 (A4), U2.6 (A5), U2.7 (A6), U2.8 (A7), U2.9 (A8), U3.1 (A1), U3.3 (A2), U3.4 (A3), U3.5 (A4), U19.6
unnamed: R29.2, U2.20 (B1)
unnamed: R30.2, U2.18 (B2)
unnamed: R31.2, U2.17 (B3)
unnamed: R32.2, U2.16 (B4)
unnamed: R33.2, U2.15 (B5)
unnamed: R34.2, U2.14 (B6)
unnamed: R35.2, U2.13 (B7)
unnamed: R36.2, U2.12 (B8)
unnamed: U3.6 (A5), U3.7 (A6), U3.8 (A7), U3.9 (A8), U4.1 (A1), U4.3 (A2), U4.4 (A3), U4.5 (A4), U4.6 (A5), U4.7 (A6), U4.8 (A7), U4.9 (A8), U19.4
unnamed: R37.2, U3.20 (B1)
unnamed: R38.2, U3.18 (B2)
unnamed: R39.2, U3.17 (B3)
unnamed: R40.2, U3.16 (B4)
unnamed: R41.2, U3.15 (B5)
unnamed: R42.2, U3.14 (B6)
unnamed: R43.2, U3.13 (B7)
unnamed: R44.2, U3.12 (B8)
unnamed: R45.2, U4.20 (B1)
unnamed: R46.2, U4.18 (B2)
unnamed: R47.2, U4.17 (B3)
unnamed: R48.2, U4.16 (B4)
unnamed: R49.2, U4.15 (B5)
unnamed: R50.2, U4.14 (B6)
unnamed: R51.2, U4.13 (B7)
unnamed: R52.2, U4.12 (B8)
unnamed: U5.1 (A1), U5.3 (A2), U5.4 (A3), U5.5 (A4), U5.6 (A5), U5.7 (A6), U5.8 (A7), U5.9 (A8), U6.1 (A1), U6.3 (A2), U6.4 (A3), U6.5 (A4), U20.6
unnamed: R53.2, U5.20 (B1)
unnamed: R54.2, U5.18 (B2)
unnamed: R55.2, U5.17 (B3)
unnamed: R56.2, U5.16 (B4)
unnamed: R57.2, U5.15 (B5)
unnamed: R58.2, U5.14 (B6)
unnamed: R59.2, U5.13 (B7)
unnamed: R60.2, U5.12 (B8)
unnamed: U6.6 (A5), U6.7 (A6), U6.8 (A7), U6.9 (A8), U7.1 (A1), U7.3 (A2), U7.4 (A3), U7.5 (A4), U7.6 (A5), U7.7 (A6), U7.8 (A7), U7.9 (A8), U20.4
unnamed: R61.2, U6.20 (B1)
unnamed: R62.2, U6.18 (B2)
unnamed: R63.2, U6.17 (B3)
unnamed: R64.2, U6.16 (B4)
unnamed: R65.2, U6.15 (B5)
unnamed: R66.2, U6.14 (B6)
unnamed: R67.2, U6.13 (B7)
unnamed: R68.2, U6.12 (B8)
unnamed: R69.2, U7.20 (B1)
unnamed: R70.2, U7.18 (B2)
unnamed: R71.2, U7.17 (B3)
unnamed: R72.2, U7.16 (B4)
unnamed: R73.2, U7.15 (B5)
unnamed: R74.2, U7.14 (B6)
unnamed: R75.2, U7.13 (B7)
unnamed: R76.2, U7.12 (B8)
unnamed: U8.1 (A1), U8.3 (A2), U8.4 (A3), U8.5 (A4), U8.6 (A5), U8.7 (A6), U8.8 (A7), U8.9 (A8), U9.1 (A1), U9.3 (A2), U9.4 (A3), U9.5 (A4), U21.6
unnamed: R77.2, U8.20 (B1)
unnamed: R78.2, U8.18 (B2)
unnamed: R79.2, U8.17 (B3)
unnamed: R80.2, U8.16 (B4)
unnamed: R81.2, U8.15 (B5)
unnamed: R82.2, U8.14 (B6)
unnamed: R83.2, U8.13 (B7)
unnamed: R84.2, U8.12 (B8)
unnamed: R85.2, U9.20 (B1)
unnamed: R86.2, U9.18 (B2)
unnamed: R87.2, U9.17 (B3)
unnamed: R88.2, U9.16 (B4)
unnamed: R89.2, U9.15 (B5)
unnamed: R90.2, U9.14 (B6)
unnamed: R91.2, U9.13 (B7)
unnamed: R92.2, U9.12 (B8)
unnamed: U9.6 (A5), U9.7 (A6), U9.8 (A7), U9.9 (A8), U10.1 (A1), U10.3 (A2), U10.4 (A3), U10.5 (A4), U10.6 (A5), U10.7 (A6), U10.8 (A7), U10.9 (A8), U21.4
unnamed: R93.2, U10.20 (B1)
unnamed: R94.2, U10.18 (B2)
unnamed: R95.2, U10.17 (B3)
unnamed: R96.2, U10.16 (B4)
unnamed: R97.2, U10.15 (B5)
unnamed: R98.2, U10.14 (B6)
unnamed: R99.2, U10.13 (B7)
unnamed: R100.2, U10.12 (B8)
unnamed: U11.1 (A1), U11.3 (A2), U11.4 (A3), U11.5 (A4), U11.6 (A5), U11.7 (A6), U11.8 (A7), U11.9 (A8), U12.1 (A1), U12.3 (A2), U12.4 (A3), U12.5 (A4), U22.6
unnamed: R101.2, U11.20 (B1)
unnamed: R102.2, U11.18 (B2)
unnamed: R103.2, U11.17 (B3)
unnamed: R104.2, U11.16 (B4)
unnamed: R105.2, U11.15 (B5)
unnamed: R106.2, U11.14 (B6)
unnamed: R107.2, U11.13 (B7)
unnamed: R108.2, U11.12 (B8)
unnamed: U12.6 (A5), U12.7 (A6), U12.8 (A7), U12.9 (A8), U13.1 (A1), U13.3 (A2), U13.4 (A3), U13.5 (A4), U13.6 (A5), U13.7 (A6), U13.8 (A7), U13.9 (A8), U22.4
unnamed: R109.2, U12.20 (B1)
unnamed: R110.2, U12.18 (B2)
unnamed: R111.2, U12.17 (B3)
unnamed: R112.2, U12.16 (B4)
unnamed: R113.2, U12.15 (B5)
unnamed: R114.2, U12.14 (B6)
unnamed: R115.2, U12.13 (B7)
unnamed: R116.2, U12.12 (B8)
unnamed: R117.2, U13.20 (B1)
unnamed: R118.2, U13.18 (B2)
unnamed: R119.2, U13.17 (B3)
unnamed: R120.2, U13.16 (B4)
unnamed: R121.2, U13.15 (B5)
unnamed: R122.2, U13.14 (B6)
unnamed: R123.2, U13.13 (B7)
unnamed: R124.2, U13.12 (B8)
unnamed: U14.1 (A1), U14.3 (A2), U23.6
unnamed: U14.4 (A3), U14.5 (A4), U23.4
unnamed: U14.6 (A5), U14.7 (A6), U24.6
unnamed: U14.8 (A7), U14.9 (A8), U24.4
unnamed: R125.2, U14.20 (B1)
unnamed: R126.2, U14.18 (B2)
unnamed: R127.2, U14.17 (B3)
unnamed: R128.2, U14.16 (B4)
unnamed: R129.2, U14.15 (B5)
unnamed: R130.2, U14.14 (B6)
unnamed: R131.2, U14.13 (B7)
unnamed: R132.2, U14.12 (B8)
unnamed: U15.1 (A1), U15.3 (A2), U25.6
unnamed: U15.4 (A3), U15.5 (A4), U25.4
unnamed: U15.6 (A5), U26.6
unnamed: U15.7 (A6), U26.4
unnamed: U15.8 (A7), U27.6
unnamed: U15.9 (A8), U27.4
unnamed: R133.2, U15.20 (B1)
unnamed: R134.2, U15.18 (B2)
unnamed: R135.2, U15.17 (B3)
unnamed: R136.2, U15.16 (B4)
unnamed: R137.2, U15.15 (B5)
unnamed: R138.2, U15.14 (B6)
unnamed: R139.2, U15.13 (B7)
unnamed: R140.2, U15.12 (B8)
unnamed: U16.1 (A1), U32.6
unnamed: U16.3 (A2), U32.4
unnamed: U16.4 (A3), U34.6
unnamed: U16.5 (A4), U34.4
unnamed: U16.6 (A5), U33.6
unnamed: U16.7 (A6), U33.4
unnamed: U16.8 (A7), U35.6
unnamed: U16.9 (A8), U35.4
unnamed: R141.2, U16.20 (B1)
unnamed: R142.2, U16.18 (B2)
unnamed: R143.2, U16.17 (B3)
unnamed: R144.2, U16.16 (B4)
unnamed: R145.2, U16.15 (B5)
unnamed: R146.2, U16.14 (B6)
unnamed: R147.2, U16.13 (B7)
unnamed: R148.2, U16.12 (B8)
unnamed: R149.1, U17.1 (A1)
unnamed: R150.1, U17.3 (A2)
unnamed: R151.1, U17.4 (A3)
unnamed: R152.1, U17.5 (A4)
unnamed: R153.1, U17.6 (A5)
unnamed: R154.1, U17.7 (A6)
unnamed: R155.1, U17.8 (A7)
unnamed: R156.1, U17.9 (A8)
unnamed: U17.20 (B1), U28.6
unnamed: U17.18 (B2), U28.4
unnamed: U17.17 (B3), U29.6
unnamed: U17.16 (B4), U29.4
unnamed: U17.15 (B5), U30.6
unnamed: U17.14 (B6), U30.4
unnamed: U17.13 (B7), U31.6
unnamed: U17.12 (B8), U31.4
unnamed: R159.2, U18.1 (A1)
unnamed: R160.2, U18.3 (A2)
unnamed: R161.2, U18.4 (A3)
unnamed: R162.2, U18.5 (A4)
unnamed: U18.6 (A5), U38.6
unnamed: U18.7 (A6), U38.4
unnamed: U18.20 (B1), U36.6
unnamed: U18.18 (B2), U36.4
unnamed: U18.17 (B3), U37.6
unnamed: U18.16 (B4), U37.4
unnamed: R157.2, U18.15 (B5)
unnamed: R158.2, U18.14 (B6)
